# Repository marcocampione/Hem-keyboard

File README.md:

# hem

A 65% ANSI keyboard PCB with an RP2040 on the board, per-key RGB and a small OLED.
The back of the PCB is a street map of central Stockholm, with a pin at home ("hem" in Swedish), 59°20'34"N 18°02'58"E.
It is meant to be seen through a clear acrylic bottom. The case files will follow.

## What's in this repo

| Folder | Contents |
|---|---|
| `pcb/` | `hem_gerbers.zip` (Gerbers + drills), `hem_bom.csv` and `hem_cpl.csv` (assembly), `hem_layers.pdf` (every layer at 1:1, for checking) |
| `pcb/kicad/` | The KiCad 10 board (`hem.kicad_pcb`), with its project and design rules |
| `firmware/hem/` | QMK keyboard definition and default keymap |
| `images/` | Renders |

## Specs

- 65% ANSI layout, 67 keys, MX switches (soldered)
- RP2040, 16 MB flash, USB-C via a Unified Daughterboard (C5 JSH or C3) on a JST-SH cable
- 67 reverse-mount SK6812MINI-E RGB LEDs, one under each switch
- 0.91" 128 x 32 SSD1306 OLED on a JST-SH connector
- PCB-mount (screw-in) stabilizers: 3 x 2u + 1 x 6.25u
- PCB: 308.8 x 99.25 mm, 2 layers

## Ordering the PCB

Upload `pcb/hem_gerbers.zip` to PCBWay or JLCPCB:
2 layers, FR-4 1.6 mm, **black** solder mask, **white** silkscreen, **ENIG**, 1 oz copper,
min track/space 0.15 mm (6 mil), min hole 0.3 mm, internal cut-outs (LED holes and slots).

For assembly, add `hem_bom.csv` and `hem_cpl.csv`.
There are 235 SMD parts on both sides: 18 on the top and 217 on the bottom.
Mark the SK6812MINI-E as **reverse-mount**.
You solder the switches yourself.

## Firmware

```
cp -r firmware/hem <qmk_firmware>/keyboards/hem
qmk compile -kb hem -km default
```

To flash: hold BOOT, plug in USB (or press RESET while holding BOOT), and copy the `.uf2` file to the `RPI-RP2` drive.

## Before the first plug-in

Measure 5 V, 3.3 V and GND for shorts with a multimeter.

## License

MIT, see `LICENSE`.
The map on the back of the PCB is made from OpenStreetMap data: © OpenStreetMap contributors, available under the
Open Database License (ODbL), https://www.openstreetmap.org/copyright

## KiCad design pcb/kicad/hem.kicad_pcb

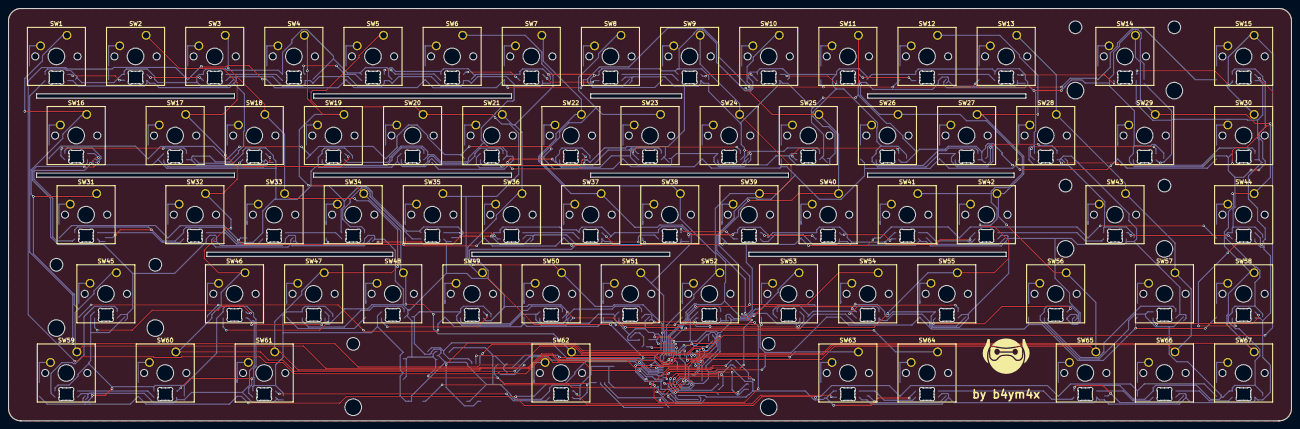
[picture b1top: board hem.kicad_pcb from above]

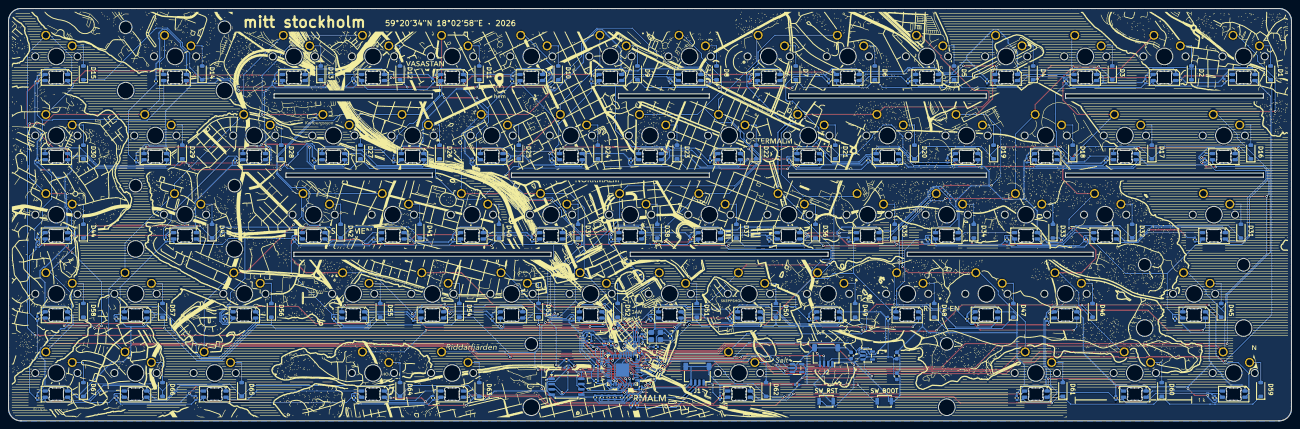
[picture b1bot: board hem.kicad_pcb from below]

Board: 2 copper layers, 308.8 x 99.2 mm, 302 parts (235 on the bottom side), 176 nets.

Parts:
C1, C2, C3, C4, C5, C6, C7, C8, C9, C10, C15, C30: 100nF; C_0402_1005Metric
C11, C12: 1uF; C_0402_1005Metric
C13, C14: 15pF; C_0402_1005Metric
C20, C21: 10uF; C_0603_1608Metric
C31: 22uF; C_0603_1608Metric
CL1, CL2, CL3, CL4, CL5, CL6, CL7, CL8, CL9, CL10, CL11, CL12, CL13, CL14, CL15, CL16, CL17, CL18, CL19, CL20, CL21, CL22, CL23, CL24, CL25, CL26, CL27, CL28, CL29, CL30, CL31, CL32, CL33, CL34, CL35, CL36, CL37, CL38, CL39, CL40, CL41, CL42, CL43, CL44, CL45, CL46, CL47, CL48, CL49, CL50, CL51, CL52, CL53, CL54, CL55, CL56, CL57, CL58, CL59, CL60, CL61, CL62, CL63, CL64, CL65, CL66, CL67: 100nF; C_0402_1005Metric
D1, D2, D3, D4, D5, D6, D7, D8, D9, D10, D11, D12, D13, D14, D15, D16, D17, D18, D19, D20, D21, D22, D23, D24, D25, D26, D27, D28, D29, D30, D31, D32, D33, D34, D35, D36, D37, D38, D39, D40, D41, D42, D43, D44, D45, D46, D47, D48, D49, D50, D51, D52, D53, D54, D55, D56, D57, D58, D59, D60, D61, D62, D63, D64, D65, D66, D67: 1N4148W; D_SOD-123
J1: uDB JST-SH; JST_SH_SM04B-SRSS-TB_1x04-1MP_P1.00mm_Horizontal
J2: OLED I2C; JST_SH_SM04B-SRSS-TB_1x04-1MP_P1.00mm_Horizontal
R3, R4: 1k; R_0402_1005Metric
R5, R6: 27; R_0402_1005Metric
R9, R10: 4.7k; R_0402_1005Metric
RGB1, RGB2, RGB3, RGB4, RGB5, RGB6, RGB7, RGB8, RGB9, RGB10, RGB11, RGB12, RGB13, RGB14, RGB15, RGB16, RGB17, RGB18, RGB19, RGB20, RGB21, RGB22, RGB23, RGB24, RGB25, RGB26, RGB27, RGB28, RGB29, RGB30, RGB31, RGB32, RGB33, RGB34, RGB35, RGB36, RGB37, RGB38, RGB39, RGB40, RGB41, RGB42, RGB43, RGB44, RGB45, RGB46, RGB47, RGB48, RGB49, RGB50, RGB51, RGB52, RGB53, RGB54, RGB55, RGB56, RGB57, RGB58, RGB59, RGB60, RGB61, RGB62, RGB63, RGB64, RGB65, RGB66, RGB67: SK6812MINI-E; LED_SK6812MINI-E_3.2x2.8mm_P1.5mm_ReverseMount
SW1: `; SW_Cherry_MX_1.00u_PCB
SW2: 1; SW_Cherry_MX_1.00u_PCB
SW3: 2; SW_Cherry_MX_1.00u_PCB
SW4: 3; SW_Cherry_MX_1.00u_PCB
SW5: 4; SW_Cherry_MX_1.00u_PCB
SW6: 5; SW_Cherry_MX_1.00u_PCB
SW7: 6; SW_Cherry_MX_1.00u_PCB
SW8: 7; SW_Cherry_MX_1.00u_PCB
SW9: 8; SW_Cherry_MX_1.00u_PCB
SW10: 9; SW_Cherry_MX_1.00u_PCB
SW11: 0; SW_Cherry_MX_1.00u_PCB
SW12: -; SW_Cherry_MX_1.00u_PCB
SW13: =; SW_Cherry_MX_1.00u_PCB
SW14: BSPC; SW_Cherry_MX_2.00u_PCB
SW15: DEL; SW_Cherry_MX_1.00u_PCB
SW16: TAB; SW_Cherry_MX_1.50u_PCB
SW17: Q; SW_Cherry_MX_1.00u_PCB
SW18: W; SW_Cherry_MX_1.00u_PCB
SW19: E; SW_Cherry_MX_1.00u_PCB
SW20: R; SW_Cherry_MX_1.00u_PCB
SW21: T; SW_Cherry_MX_1.00u_PCB
SW22: Y; SW_Cherry_MX_1.00u_PCB
SW23: U; SW_Cherry_MX_1.00u_PCB
SW24: I; SW_Cherry_MX_1.00u_PCB
SW25: O; SW_Cherry_MX_1.00u_PCB
SW26: P; SW_Cherry_MX_1.00u_PCB
SW27: [; SW_Cherry_MX_1.00u_PCB
SW28: ]; SW_Cherry_MX_1.00u_PCB
SW29: \; SW_Cherry_MX_1.50u_PCB
SW30: PGUP; SW_Cherry_MX_1.00u_PCB
SW31: CAPS; SW_Cherry_MX_1.75u_PCB
SW32: A; SW_Cherry_MX_1.00u_PCB
SW33: S; SW_Cherry_MX_1.00u_PCB
SW34: D; SW_Cherry_MX_1.00u_PCB
SW35: F; SW_Cherry_MX_1.00u_PCB
SW36: G; SW_Cherry_MX_1.00u_PCB
SW37: H; SW_Cherry_MX_1.00u_PCB
SW38: J; SW_Cherry_MX_1.00u_PCB
SW39: K; SW_Cherry_MX_1.00u_PCB
SW40: L; SW_Cherry_MX_1.00u_PCB
SW41: ;; SW_Cherry_MX_1.00u_PCB
SW42: '; SW_Cherry_MX_1.00u_PCB
SW43: ENT; SW_Cherry_MX_2.25u_PCB
SW44: PGDN; SW_Cherry_MX_1.00u_PCB
SW45: LSFT; SW_Cherry_MX_2.25u_PCB
SW46: Z; SW_Cherry_MX_1.00u_PCB
SW47: X; SW_Cherry_MX_1.00u_PCB
SW48: C; SW_Cherry_MX_1.00u_PCB
SW49: V; SW_Cherry_MX_1.00u_PCB
SW50: B; SW_Cherry_MX_1.00u_PCB
SW51: N; SW_Cherry_MX_1.00u_PCB
SW52: M; SW_Cherry_MX_1.00u_PCB
SW53: ,; SW_Cherry_MX_1.00u_PCB
SW54: .; SW_Cherry_MX_1.00u_PCB
SW55: /; SW_Cherry_MX_1.00u_PCB
SW56: RSFT; SW_Cherry_MX_1.75u_PCB
SW57: UP; SW_Cherry_MX_1.00u_PCB
SW58: END; SW_Cherry_MX_1.00u_PCB
SW59: LCTL; SW_Cherry_MX_1.25u_PCB
SW60: LGUI; SW_Cherry_MX_1.25u_PCB
SW61: LALT; SW_Cherry_MX_1.25u_PCB
SW62: SPC; SW_Cherry_MX_6.25u_PCB
SW63: RALT; SW_Cherry_MX_1.00u_PCB
SW64: FN; SW_Cherry_MX_1.00u_PCB
SW65: LEFT; SW_Cherry_MX_1.00u_PCB
SW66: DOWN; SW_Cherry_MX_1.00u_PCB
SW67: RGHT; SW_Cherry_MX_1.00u_PCB
SW_BOOT: BOOTSEL; SW_SPST_B3U-1000P
SW_RST: RESET; SW_SPST_B3U-1000P
U1: RP2040; QFN-56-1EP_7x7mm_P0.4mm_EP3.2x3.2mm
U2: AP2112K-3.3; SOT-23-5
U3: W25Q128JVS; SOIC-8_5.3x5.3mm_P1.27mm
U4: 74AHCT1G125; SOT-23-5
Y1: 12MHz; Crystal_SMD_3225-4Pin_3.2x2.5mm

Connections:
1V1: C6.1, C8.1, C12.1, U1.23, U1.45, U1.50
3V3: C1.1, C2.1, C3.1, C4.1, C5.1, C7.1, C9.1, C10.1, C11.1, C15.1, C21.1, J2.2, R9.2, R10.2, U1.1, U1.10, U1.22, U1.33, U1.42, U1.43, U1.44, U1.48, U1.49, U2.5, U3.8
BOOT: R4.2, SW_BOOT.1
COL0: SW1.1, SW16.1, SW31.1, SW45.1, SW59.1, U1.7
COL1: SW2.1, SW17.1, SW32.1, SW46.1, SW60.1, U1.8
COL2: SW3.1, SW18.1, SW33.1, SW47.1, SW61.1, U1.9
COL3: SW4.1, SW19.1, SW34.1, SW48.1, SW62.1, U1.11
COL4: SW5.1, SW20.1, SW35.1, SW49.1, SW63.1, U1.12
COL5: SW6.1, SW21.1, SW36.1, SW50.1, SW64.1, U1.13
COL6: SW7.1, SW22.1, SW37.1, SW51.1, U1.14
COL7: SW8.1, SW23.1, SW38.1, SW52.1, U1.15
COL8: SW9.1, SW24.1, SW39.1, SW53.1, U1.16
COL9: SW10.1, SW25.1, SW40.1, SW54.1, U1.17
COL10: SW11.1, SW26.1, SW41.1, SW55.1, U1.18
COL11: SW12.1, SW27.1, SW42.1, SW56.1, SW65.1, U1.27
COL12: SW13.1, SW28.1, SW43.1, SW57.1, SW66.1, U1.28
COL13: SW14.1, SW29.1, SW44.1, SW58.1, SW67.1, U1.29
COL14: SW15.1, SW30.1, U1.30
D1: D1.2, SW1.2
D2: D2.2, SW2.2
D3: D3.2, SW3.2
D4: D4.2, SW4.2
D5: D5.2, SW5.2
D6: D6.2, SW6.2
D7: D7.2, SW7.2
D8: D8.2, SW8.2
D9: D9.2, SW9.2
D10: D10.2, SW10.2
D11: D11.2, SW11.2
D12: D12.2, SW12.2
D13: D13.2, SW13.2
D14: D14.2, SW14.2
D15: D15.2, SW15.2
D16: D16.2, SW16.2
D17: D17.2, SW17.2
D18: D18.2, SW18.2
D19: D19.2, SW19.2
D20: D20.2, SW20.2
D21: D21.2, SW21.2
D22: D22.2, SW22.2
D23: D23.2, SW23.2
D24: D24.2, SW24.2
D25: D25.2, SW25.2
D26: D26.2, SW26.2
D27: D27.2, SW27.2
D28: D28.2, SW28.2
D29: D29.2, SW29.2
D30: D30.2, SW30.2
D31: D31.2, SW31.2
D32: D32.2, SW32.2
D33: D33.2, SW33.2
D34: D34.2, SW34.2
D35: D35.2, SW35.2
D36: D36.2, SW36.2
D37: D37.2, SW37.2
D38: D38.2, SW38.2
D39: D39.2, SW39.2
D40: D40.2, SW40.2
D41: D41.2, SW41.2
D42: D42.2, SW42.2
D43: D43.2, SW43.2
D44: D44.2, SW44.2
D45: D45.2, SW45.2
D46: D46.2, SW46.2
D47: D47.2, SW47.2
D48: D48.2, SW48.2
D49: D49.2, SW49.2
D50: D50.2, SW50.2
D51: D51.2, SW51.2
D52: D52.2, SW52.2
D53: D53.2, SW53.2
D54: D54.2, SW54.2
D55: D55.2, SW55.2
D56: D56.2, SW56.2
D57: D57.2, SW57.2
D58: D58.2, SW58.2
D59: D59.2, SW59.2
D60: D60.2, SW60.2
D61: D61.2, SW61.2
D62: D62.2, SW62.2
D63: D63.2, SW63.2
D64: D64.2, SW64.2
D65: D65.2, SW65.2
D66: D66.2, SW66.2
D67: D67.2, SW67.2
GND: C1.2, C2.2, C3.2, C4.2, C5.2, C6.2, C7.2, C8.2, C9.2, C10.2, C11.2, C12.2, C13.2, C14.2, C15.2, C20.2, C21.2, C30.2, C31.2, CL1.2, CL2.2, CL3.2, CL4.2, CL5.2, CL6.2, CL7.2, CL8.2, CL9.2, CL10.2, CL11.2, CL12.2, CL13.2, CL14.2, CL15.2, CL16.2, CL17.2, CL18.2, CL19.2, CL20.2, CL21.2, CL22.2, CL23.2, CL24.2, CL25.2, CL26.2, CL27.2, CL28.2, CL29.2, CL30.2, CL31.2, CL32.2, CL33.2, CL34.2, CL35.2, CL36.2, CL37.2, CL38.2, CL39.2, CL40.2, CL41.2, CL42.2, CL43.2, CL44.2, CL45.2, CL46.2, CL47.2, CL48.2, CL49.2, CL50.2, CL51.2, CL52.2, CL53.2, CL54.2, CL55.2, CL56.2, CL57.2, CL58.2, CL59.2, CL60.2, CL61.2, CL62.2, CL63.2, CL64.2, CL65.2, CL66.2, CL67.2, J1.4, J1.MP, J2.1, J2.MP, RGB1.1, RGB2.1, RGB3.1, RGB4.1, RGB5.1, RGB6.1, RGB7.1, RGB8.1, RGB9.1, RGB10.1, RGB11.1, RGB12.1, RGB13.1, RGB14.1, RGB15.1, RGB16.1, RGB17.1, RGB18.1, RGB19.1, RGB20.1, RGB21.1, RGB22.1, RGB23.1, RGB24.1, RGB25.1, RGB26.1, RGB27.1, RGB28.1, RGB29.1, RGB30.1, RGB31.1, RGB32.1, RGB33.1, RGB34.1, RGB35.1, RGB36.1, RGB37.1, RGB38.1, RGB39.1, RGB40.1, RGB41.1, RGB42.1, RGB43.1, RGB44.1, RGB45.1, RGB46.1, RGB47.1, RGB48.1, RGB49.1, RGB50.1, RGB51.1, RGB52.1, RGB53.1, RGB54.1, RGB55.1, RGB56.1, RGB57.1, RGB58.1, RGB59.1, RGB60.1, RGB61.1, RGB62.1, RGB63.1, RGB64.1, RGB65.1, RGB66.1, RGB67.1, SW_BOOT.2, SW_RST.2, U1.19, U1.57, U2.2, U3.4, U4.1, U4.3, Y1.2, Y1.4
LD0: RGB1.2, U4.4
LD1: RGB1.4, RGB2.2
LD2: RGB2.4, RGB3.2
LD3: RGB3.4, RGB4.2
LD4: RGB4.4, RGB5.2
LD5: RGB5.4, RGB6.2
LD6: RGB6.4, RGB7.2
LD7: RGB7.4, RGB8.2
LD8: RGB8.4, RGB9.2
LD9: RGB9.4, RGB10.2
LD10: RGB10.4, RGB11.2
LD11: RGB11.4, RGB12.2
LD12: RGB12.4, RGB13.2
LD13: RGB13.4, RGB14.2
LD14: RGB14.4, RGB15.2
LD15: RGB15.4, RGB30.2
LD16: RGB29.2, RGB30.4
LD17: RGB28.2, RGB29.4
LD18: RGB27.2, RGB28.4
LD19: RGB26.2, RGB27.4
LD20: RGB25.2, RGB26.4
LD21: RGB24.2, RGB25.4
LD22: RGB23.2, RGB24.4
LD23: RGB22.2, RGB23.4
LD24: RGB21.2, RGB22.4
LD25: RGB20.2, RGB21.4
LD26: RGB19.2, RGB20.4
LD27: RGB18.2, RGB19.4
LD28: RGB17.2, RGB18.4
LD29: RGB16.2, RGB17.4
LD30: RGB16.4, RGB31.2
LD31: RGB31.4, RGB32.2
LD32: RGB32.4, RGB33.2
LD33: RGB33.4, RGB34.2
LD34: RGB34.4, RGB35.2
LD35: RGB35.4, RGB36.2
LD36: RGB36.4, RGB37.2
LD37: RGB37.4, RGB38.2
LD38: RGB38.4, RGB39.2
LD39: RGB39.4, RGB40.2
LD40: RGB40.4, RGB41.2
LD41: RGB41.4, RGB42.2
LD42: RGB42.4, RGB43.2
LD43: RGB43.4, RGB44.2
LD44: RGB44.4, RGB58.2
LD45: RGB57.2, RGB58.4
LD46: RGB56.2, RGB57.4
LD47: RGB55.2, RGB56.4
LD48: RGB54.2, RGB55.4
LD49: RGB53.2, RGB54.4
LD50: RGB52.2, RGB53.4
LD51: RGB51.2, RGB52.4
LD52: RGB50.2, RGB51.4
LD53: RGB49.2, RGB50.4
LD54: RGB48.2, RGB49.4
LD55: RGB47.2, RGB48.4
LD56: RGB46.2, RGB47.4
LD57: RGB45.2, RGB46.4
LD58: RGB45.4, RGB59.2
LD59: RGB59.4, RGB60.2
LD60: RGB60.4, RGB61.2
LD61: RGB61.4, RGB62.2
LD62: RGB62.4, RGB63.2
LD63: RGB63.4, RGB64.2
LD64: RGB64.4, RGB65.2
LD65: RGB65.4, RGB66.2
LD66: RGB66.4, RGB67.2
QSPI_SCLK: U1.52, U3.6
QSPI_SD0: U1.53, U3.5
QSPI_SD1: U1.55, U3.2
QSPI_SD2: U1.54, U3.3
QSPI_SD3: U1.51, U3.7
QSPI_SS: R4.1, U1.56, U3.1
RGB_3V3: U1.31, U4.2
ROW0: D1.1, D2.1, D3.1, D4.1, D5.1, D6.1, D7.1, D8.1, D9.1, D10.1, D11.1, D12.1, D13.1, D14.1, D15.1, U1.2
ROW1: D16.1, D17.1, D18.1, D19.1, D20.1, D21.1, D22.1, D23.1, D24.1, D25.1, D26.1, D27.1, D28.1, D29.1, D30.1, U1.3
ROW2: D31.1, D32.1, D33.1, D34.1, D35.1, D36.1, D37.1, D38.1, D39.1, D40.1, D41.1, D42.1, D43.1, D44.1, U1.4
ROW3: D45.1, D46.1, D47.1, D48.1, D49.1, D50.1, D51.1, D52.1, D53.1, D54.1, D55.1, D56.1, D57.1, D58.1, U1.5
ROW4: D59.1, D60.1, D61.1, D62.1, D63.1, D64.1, D65.1, D66.1, D67.1, U1.6
RUN: SW_RST.1, U1.26
SCL: J2.3, R10.1, U1.39
SDA: J2.4, R9.1, U1.38
UDM: J1.2, R6.1
UDP: J1.3, R5.1
USB_DM: R6.2, U1.46
USB_DP: R5.2, U1.47
VBUS: C20.1, C30.1, C31.1, CL1.1, CL2.1, CL3.1, CL4.1, CL5.1, CL6.1, CL7.1, CL8.1, CL9.1, CL10.1, CL11.1, CL12.1, CL13.1, CL14.1, CL15.1, CL16.1, CL17.1, CL18.1, CL19.1, CL20.1, CL21.1, CL22.1, CL23.1, CL24.1, CL25.1, CL26.1, CL27.1, CL28.1, CL29.1, CL30.1, CL31.1, CL32.1, CL33.1, CL34.1, CL35.1, CL36.1, CL37.1, CL38.1, CL39.1, CL40.1, CL41.1, CL42.1, CL43.1, CL44.1, CL45.1, CL46.1, CL47.1, CL48.1, CL49.1, CL50.1, CL51.1, CL52.1, CL53.1, CL54.1, CL55.1, CL56.1, CL57.1, CL58.1, CL59.1, CL60.1, CL61.1, CL62.1, CL63.1, CL64.1, CL65.1, CL66.1, CL67.1, J1.1, RGB1.3, RGB2.3, RGB3.3, RGB4.3, RGB5.3, RGB6.3, RGB7.3, RGB8.3, RGB9.3, RGB10.3, RGB11.3, RGB12.3, RGB13.3, RGB14.3, RGB15.3, RGB16.3, RGB17.3, RGB18.3, RGB19.3, RGB20.3, RGB21.3, RGB22.3, RGB23.3, RGB24.3, RGB25.3, RGB26.3, RGB27.3, RGB28.3, RGB29.3, RGB30.3, RGB31.3, RGB32.3, RGB33.3, RGB34.3, RGB35.3, RGB36.3, RGB37.3, RGB38.3, RGB39.3, RGB40.3, RGB41.3, RGB42.3, RGB43.3, RGB44.3, RGB45.3, RGB46.3, RGB47.3, RGB48.3, RGB49.3, RGB50.3, RGB51.3, RGB52.3, RGB53.3, RGB54.3, RGB55.3, RGB56.3, RGB57.3, RGB58.3, RGB59.3, RGB60.3, RGB61.3, RGB62.3, RGB63.3, RGB64.3, RGB65.3, RGB66.3, RGB67.3, U2.1, U2.3, U4.5
XI: C13.1, U1.20, Y1.1
XO: R3.1, U1.21
XO2: C14.1, R3.2, Y1.3

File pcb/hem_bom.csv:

Item,Designator,Qty,Manufacturer,Mfg Part #,Description / Value,Package,Side,Type
1,"RGB1,RGB2,RGB3,RGB4,RGB5,RGB6,RGB7,RGB8,RGB9,RGB10,RGB11,RGB12,RGB13,RGB14,RGB15,RGB16,RGB17,RGB18,RGB19,RGB20,RGB21,RGB22,RGB23,RGB24,RGB25,RGB26,RGB27,RGB28,RGB29,RGB30,RGB31,RGB32,RGB33,RGB34,RGB35,RGB36,RGB37,RGB38,RGB39,RGB40,RGB41,RGB42,RGB43,RGB44,RGB45,RGB46,RGB47,RGB48,RGB49,RGB50,RGB51,RGB52,RGB53,RGB54,RGB55,RGB56,RGB57,RGB58,RGB59,RGB60,RGB61,RGB62,RGB63,RGB64,RGB65,RGB66,RGB67",67,OPSCO,SK6812MINI-E,"SK6812MINI-E: RGB LED, REVERSE MOUNT on the back (lens through the PCB cutout)",LED_SK6812MINI-E_3.2x2.8mm_P1.5mm_ReverseMount,bottom,SMD
2,"D1,D2,D3,D4,D5,D6,D7,D8,D9,D10,D11,D12,D13,D14,D15,D16,D17,D18,D19,D20,D21,D22,D23,D24,D25,D26,D27,D28,D29,D30,D31,D32,D33,D34,D35,D36,D37,D38,D39,D40,D41,D42,D43,D44,D45,D46,D47,D48,D49,D50,D51,D52,D53,D54,D55,D56,D57,D58,D59,D60,D61,D62,D63,D64,D65,D66,D67",67,Diodes Inc,1N4148W-7-F,1N4148W: switching diode SOD-123,D_SOD-123,bottom,SMD
3,"C1,C2,C3,C4,C5,C6,C7,C8,C9,C10,C15,C30,CL1,CL2,CL3,CL4,CL5,CL6,CL7,CL8,CL9,CL10,CL11,CL12,CL13,CL14,CL15,CL16,CL17,CL18,CL19,CL20,CL21,CL22,CL23,CL24,CL25,CL26,CL27,CL28,CL29,CL30,CL31,CL32,CL33,CL34,CL35,CL36,CL37,CL38,CL39,CL40,CL41,CL42,CL43,CL44,CL45,CL46,CL47,CL48,CL49,CL50,CL51,CL52,CL53,CL54,CL55,CL56,CL57,CL58,CL59,CL60,CL61,CL62,CL63,CL64,CL65,CL66,CL67",79,Samsung,CL05B104KO5NNNC,100nF: 100 nF 16 V X7R 0402,C_0402_1005Metric,bottom,SMD
4,Y1,1,Abracon,ABM8-272-T3,12MHz: crystal 12 MHz 10 pF 3225 (RP2040 reference part),Crystal_SMD_3225-4Pin_3.2x2.5mm,bottom,SMD
5,"C11,C12",2,Samsung,CL05A105KA5NQNC,1uF: 1 uF 25 V X5R 0402,C_0402_1005Metric,bottom,SMD
6,C31,1,Samsung,CL10A226MP8NUNE,22uF: 22 uF 10 V X5R 0603,C_0603_1608Metric,bottom,SMD
7,"C13,C14",2,Samsung,CL05C150JB5NNNC,15pF: 15 pF 50 V C0G 0402,C_0402_1005Metric,bottom,SMD
8,"C20,C21",2,Samsung,CL10A106KO8NNNC,10uF: 10 uF 16 V X5R 0603,C_0603_1608Metric,bottom,SMD
9,"R5,R6",2,Yageo,RC0402FR-0727RL,27: 27 R 1% 0402,R_0402_1005Metric,bottom,SMD
10,J1,1,JST,SM04B-SRSS-TB(LF)(SN),uDB JST-SH: 4-pin 1 mm right-angle header (USB daughterboard),JST_SH_SM04B-SRSS-TB_1x04-1MP_P1.00mm_Horizontal,bottom,SMD
11,SW_RST,1,Omron,B3U-1000P,"RESET: tactile switch, SMD",SW_SPST_B3U-1000P,bottom,SMD
12,U3,1,Winbond,W25Q128JVSIQ,"W25Q128JVS: 16 MB QSPI flash, SOIC-8 208 mil",SOIC-8_5.3x5.3mm_P1.27mm,bottom,SMD
13,"R9,R10",2,Yageo,RC0402FR-074K7L,4.7k: 4.7 k 1% 0402,R_0402_1005Metric,bottom,SMD
14,U2,1,Diodes Inc,AP2112K-3.3TRG1,AP2112K-3.3: LDO 3.3 V 600 mA,SOT-23-5,bottom,SMD
15,U4,1,Texas Instruments,SN74AHCT1G125DBVR,"74AHCT1G125: buffer, 3.3 V -> 5 V level shift for the LED data",SOT-23-5,bottom,SMD
16,"R3,R4",2,Yageo,RC0402FR-071KL,1k: 1 k 1% 0402,R_0402_1005Metric,bottom,SMD
17,U1,1,Raspberry Pi,RP2040,"RP2040: MCU, dual Cortex-M0+, QFN-56 7x7",QFN-56-1EP_7x7mm_P0.4mm_EP3.2x3.2mm,bottom,SMD
18,J2,1,JST,SM04B-SRSS-TB(LF)(SN),OLED I2C: 4-pin 1 mm right-angle header (OLED),JST_SH_SM04B-SRSS-TB_1x04-1MP_P1.00mm_Horizontal,bottom,SMD
19,SW_BOOT,1,Omron,B3U-1000P,"BOOTSEL: tactile switch, SMD",SW_SPST_B3U-1000P,bottom,SMD
